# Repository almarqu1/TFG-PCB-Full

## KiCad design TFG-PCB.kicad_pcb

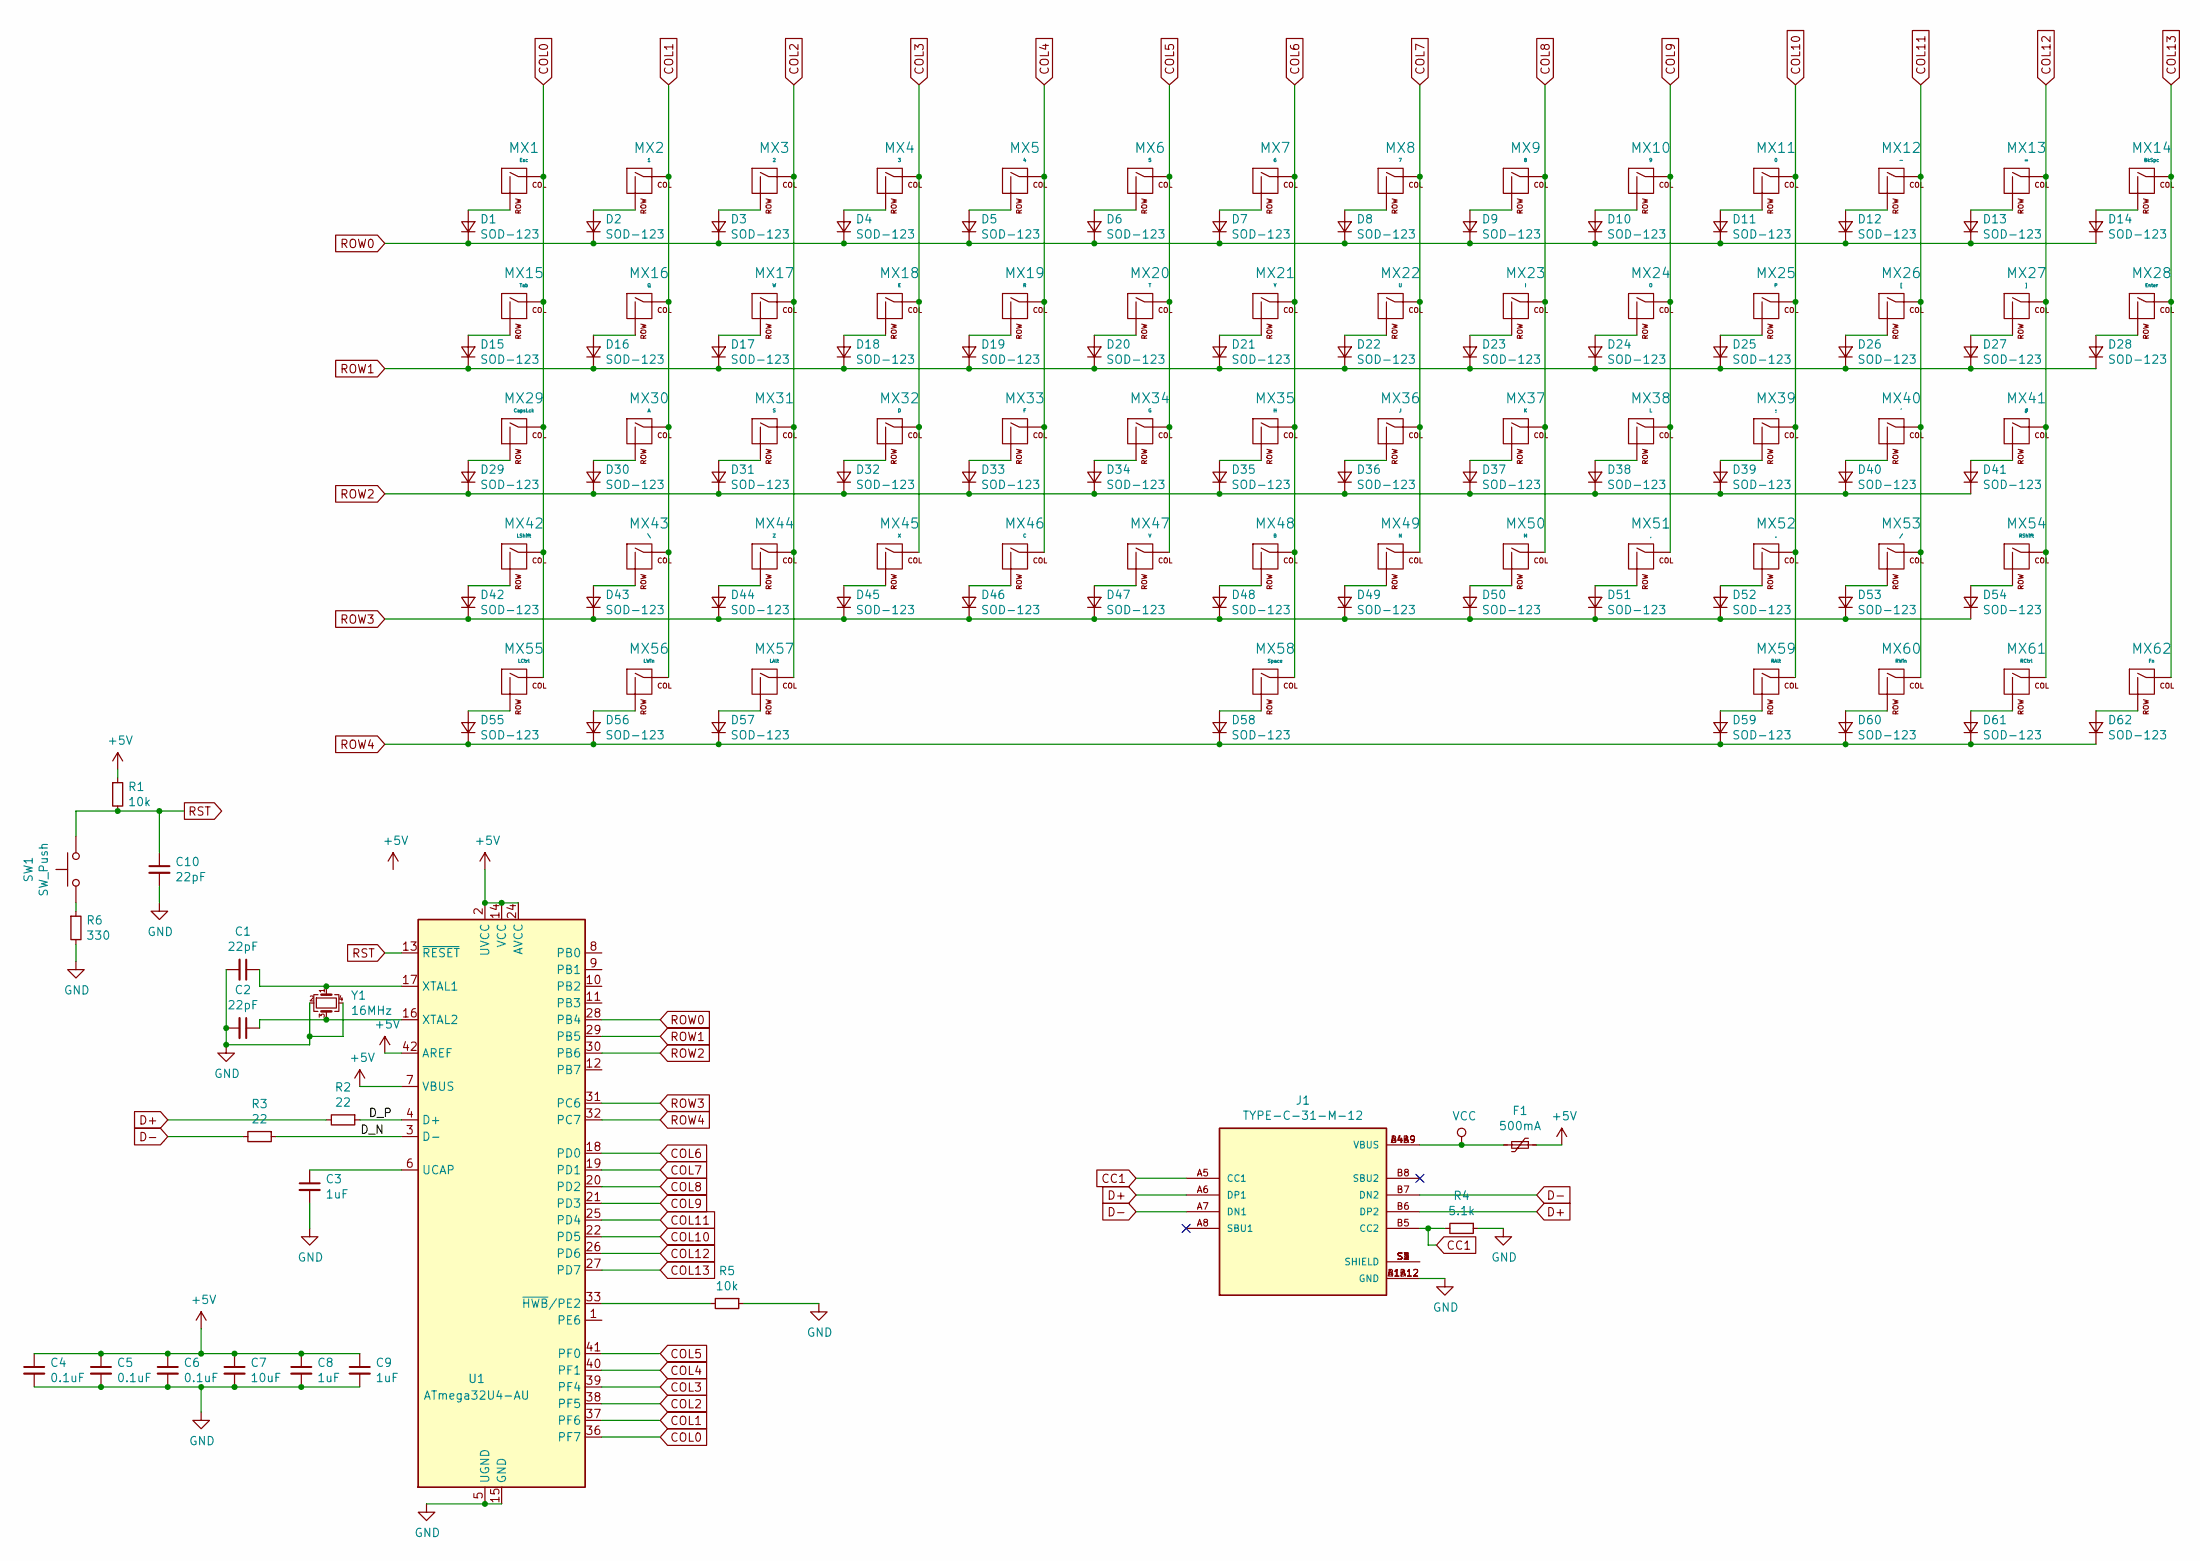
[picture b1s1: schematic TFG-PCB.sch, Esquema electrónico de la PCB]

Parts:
C1, C2, C10: 22pF; C_0805_2012Metric
C3, C8, C9: 1uF; C_0805_2012Metric
C4, C5, C6: 0.1uF; C_0805_2012Metric
C7: 10uF; C_0805_2012Metric
D1, D2, D3, D4, D5, D6, D7, D8, D9, D10, D11, D12, D13, D14, D15, D16, D17, D18, D19, D20, D21, D22, D23, D24, D25, D26, D27, D28, D29, D30, D31, D32, D33, D34, D35, D36, D37, D38, D39, D40, D41, D42, D43, D44, D45, D46, D47, D48, D49, D50, D51, D52, D53, D54, D55, D56, D57, D58, D59, D60, D61, D62: SOD-123; D_SOD-123
F1: 500mA; Fuse_1206_3216Metric
J1: TYPE-C-31-M-12; HRO_TYPE-C-31-M-12; PARTREV A
MX1: Esc; MXOnly-1U
MX2: 1; MXOnly-1U
MX3: 2; MXOnly-1U
MX4: 3; MXOnly-1U
MX5: 4; MXOnly-1U
MX6: 5; MXOnly-1U
MX7: 6; MXOnly-1U
MX8: 7; MXOnly-1U
MX9: 8; MXOnly-1U
MX10: 9; MXOnly-1U
MX11: 0; MXOnly-1U
MX12: -; MXOnly-1U
MX13: =; MXOnly-1U
MX14: BkSpc; MXOnly-2U
MX15: Tab; MXOnly-1.5U
MX16: Q; MXOnly-1U
MX17: W; MXOnly-1U
MX18: E; MXOnly-1U
MX19: R; MXOnly-1U
MX20: T; MXOnly-1U
MX21: Y; MXOnly-1U
MX22: U; MXOnly-1U
MX23: I; MXOnly-1U
MX24: O; MXOnly-1U
MX25: P; MXOnly-1U
MX26: [; MXOnly-1U
MX27: ]; MXOnly-1U
MX28: Enter; MXOnly-ISO
MX29: CapsLck; MXOnly-1.75U
MX30: A; MXOnly-1U
MX31: S; MXOnly-1U
MX32: D; MXOnly-1U
MX33: F; MXOnly-1U
MX34: G; MXOnly-1U
MX35: H; MXOnly-1U
MX36: J; MXOnly-1U
MX37: K; MXOnly-1U
MX38: L; MXOnly-1U
MX39: ;; MXOnly-1U
MX40: '; MXOnly-1U
MX41: #; MXOnly-1U
MX42: LShift; MXOnly-1.25U
MX43: \\; MXOnly-1U
MX44: Z; MXOnly-1U
MX45: X; MXOnly-1U
MX46: C; MXOnly-1U
MX47: V; MXOnly-1U
MX48: B; MXOnly-1U
MX49: N; MXOnly-1U
MX50: M; MXOnly-1U
MX51: ,; MXOnly-1U
MX52: .; MXOnly-1U
MX53: /; MXOnly-1U
MX54: RShift; MXOnly-2.75U
MX55: LCtrl; MXOnly-1.25U
MX56: LWin; MXOnly-1.25U
MX57: LAlt; MXOnly-1.25U
MX58: Space; MXOnly-6.25U
MX59: RAlt; MXOnly-1.25U
MX60: RWin; MXOnly-1.25U
MX61: RCtrl; MXOnly-1.25U
MX62: Fn; MXOnly-1.25U
R1, R5: 10k; R_0805_2012Metric
R2, R3: 22; R_0805_2012Metric
R4: 5.1k; R_0805_2012Metric
R6: 330; R_0805_2012Metric
SW1: SW_Push; SKQG-1155865
U1: ATmega32U4-AU; TQFP-44_10x10mm_P0.8mm
Y1: 16MHz; Crystal_SMD_3225-4Pin_3.2x2.5mm

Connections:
+5V: C4.1, C5.1, C6.1, C7.1, C8.1, C9.1, F1.1, R1.1, U1.2 (UVCC), U1.7 (VBUS), U1.14 (VCC), U1.24 (AVCC), U1.34 (VCC), U1.42 (AREF), U1.44 (AVCC)
/D_N: R3.1, U1.3 (D-)
/D_P: R2.1, U1.4 (D+)
CC1: J1.A5 (CC1), J1.B5 (CC2), R4.2
COL0: MX1.1 (COL), MX15.1 (COL), MX29.1 (COL), MX42.1 (COL), MX55.1 (COL), U1.36 (PF7)
COL1: MX2.1 (COL), MX16.1 (COL), MX30.1 (COL), MX43.1 (COL), MX56.1 (COL), U1.37 (PF6)
COL2: MX3.1 (COL), MX17.1 (COL), MX31.1 (COL), MX44.1 (COL), MX57.1 (COL), U1.38 (PF5)
COL3: MX4.1 (COL), MX18.1 (COL), MX32.1 (COL), MX45.1 (COL), U1.39 (PF4)
COL4: MX5.1 (COL), MX19.1 (COL), MX33.1 (COL), MX46.1 (COL), U1.40 (PF1)
COL5: MX6.1 (COL), MX20.1 (COL), MX34.1 (COL), MX47.1 (COL), U1.41 (PF0)
COL6: MX7.1 (COL), MX21.1 (COL), MX35.1 (COL), MX48.1 (COL), MX58.1 (COL), U1.18 (PD0)
COL7: MX8.1 (COL), MX22.1 (COL), MX36.1 (COL), MX49.1 (COL), U1.19 (PD1)
COL8: MX9.1 (COL), MX23.1 (COL), MX37.1 (COL), MX50.1 (COL), U1.20 (PD2)
COL9: MX10.1 (COL), MX24.1 (COL), MX38.1 (COL), MX51.1 (COL), U1.21 (PD3)
COL10: MX11.1 (COL), MX25.1 (COL), MX39.1 (COL), MX52.1 (COL), MX59.1 (COL), U1.22 (PD5)
COL11: MX12.1 (COL), MX26.1 (COL), MX40.1 (COL), MX53.1 (COL), MX60.1 (COL), U1.25 (PD4)
COL12: MX13.1 (COL), MX27.1 (COL), MX41.1 (COL), MX54.1 (COL), MX61.1 (COL), U1.26 (PD6)
COL13: MX14.1 (COL), MX28.1 (COL), MX62.1 (COL), U1.27 (PD7)
D+: J1.A6 (DP1), J1.B6 (DP2), R2.2
D-: J1.A7 (DN1), J1.B7 (DN2), R3.2
GND: C1.2, C2.2, C3.2, C4.2, C5.2, C6.2, C7.2, C8.2, C9.2, C10.2, J1.A1B12 (GND), J1.B1A12 (GND), R4.1, R5.1, R6.2, U1.5 (UGND), U1.15 (GND), U1.23 (GND), U1.35 (GND), U1.43 (GND), Y1.2, Y1.4
unnamed: C1.1, U1.17 (XTAL1), Y1.1
unnamed: C2.1, U1.16 (XTAL2), Y1.3
unnamed: C3.1, U1.6 (UCAP)
unnamed: D1.2 (A), MX1.2 (ROW)
unnamed: D2.2 (A), MX2.2 (ROW)
unnamed: D3.2 (A), MX3.2 (ROW)
unnamed: D4.2 (A), MX4.2 (ROW)
unnamed: D5.2 (A), MX5.2 (ROW)
unnamed: D6.2 (A), MX6.2 (ROW)
unnamed: D7.2 (A), MX7.2 (ROW)
unnamed: D8.2 (A), MX8.2 (ROW)
unnamed: D9.2 (A), MX9.2 (ROW)
unnamed: D10.2 (A), MX10.2 (ROW)
unnamed: D11.2 (A), MX11.2 (ROW)
unnamed: D12.2 (A), MX12.2 (ROW)
unnamed: D13.2 (A), MX13.2 (ROW)
unnamed: D14.2 (A), MX14.2 (ROW)
unnamed: D15.2 (A), MX15.2 (ROW)
unnamed: D16.2 (A), MX16.2 (ROW)
unnamed: D17.2 (A), MX17.2 (ROW)
unnamed: D18.2 (A), MX18.2 (ROW)
unnamed: D19.2 (A), MX19.2 (ROW)
unnamed: D20.2 (A), MX20.2 (ROW)
unnamed: D21.2 (A), MX21.2 (ROW)
unnamed: D22.2 (A), MX22.2 (ROW)
unnamed: D23.2 (A), MX23.2 (ROW)
unnamed: D24.2 (A), MX24.2 (ROW)
unnamed: D25.2 (A), MX25.2 (ROW)
unnamed: D26.2 (A), MX26.2 (ROW)
unnamed: D27.2 (A), MX27.2 (ROW)
unnamed: D28.2 (A), MX28.2 (ROW)
unnamed: D29.2 (A), MX29.2 (ROW)
unnamed: D30.2 (A), MX30.2 (ROW)
unnamed: D31.2 (A), MX31.2 (ROW)
unnamed: D32.2 (A), MX32.2 (ROW)
unnamed: D33.2 (A), MX33.2 (ROW)
unnamed: D34.2 (A), MX34.2 (ROW)
unnamed: D35.2 (A), MX35.2 (ROW)
unnamed: D36.2 (A), MX36.2 (ROW)
unnamed: D37.2 (A), MX37.2 (ROW)
unnamed: D38.2 (A), MX38.2 (ROW)
unnamed: D39.2 (A), MX39.2 (ROW)
unnamed: D40.2 (A), MX40.2 (ROW)
unnamed: D41.2 (A), MX41.2 (ROW)
unnamed: D42.2 (A), MX42.2 (ROW)
unnamed: D43.2 (A), MX43.2 (ROW)
unnamed: D44.2 (A), MX44.2 (ROW)
unnamed: D45.2 (A), MX45.2 (ROW)
unnamed: D46.2 (A), MX46.2 (ROW)
unnamed: D47.2 (A), MX47.2 (ROW)
unnamed: D48.2 (A), MX48.2 (ROW)
unnamed: D49.2 (A), MX49.2 (ROW)
unnamed: D50.2 (A), MX50.2 (ROW)
unnamed: D51.2 (A), MX51.2 (ROW)
unnamed: D52.2 (A), MX52.2 (ROW)
unnamed: D53.2 (A), MX53.2 (ROW)
unnamed: D54.2 (A), MX54.2 (ROW)
unnamed: D55.2 (A), MX55.2 (ROW)
unnamed: D56.2 (A), MX56.2 (ROW)
unnamed: D57.2 (A), MX57.2 (ROW)
unnamed: D58.2 (A), MX58.2 (ROW)
unnamed: D59.2 (A), MX59.2 (ROW)
unnamed: D60.2 (A), MX60.2 (ROW)
unnamed: D61.2 (A), MX61.2 (ROW)
unnamed: D62.2 (A), MX62.2 (ROW)
unnamed: J1.S1 (SHIELD), J1.S2 (SHIELD), J1.S3 (SHIELD), J1.S4 (SHIELD)
unnamed: R5.2, U1.33 (~HWB~/PE2)
unnamed: R6.1, SW1.1
ROW0: D1.1 (K), D2.1 (K), D3.1 (K), D4.1 (K), D5.1 (K), D6.1 (K), D7.1 (K), D8.1 (K), D9.1 (K), D10.1 (K), D11.1 (K), D12.1 (K), D13.1 (K), D14.1 (K), U1.28 (PB4)
ROW1: D15.1 (K), D16.1 (K), D17.1 (K), D18.1 (K), D19.1 (K), D20.1 (K), D21.1 (K), D22.1 (K), D23.1 (K), D24.1 (K), D25.1 (K), D26.1 (K), D27.1 (K), D28.1 (K), U1.29 (PB5)
ROW2: D29.1 (K), D30.1 (K), D31.1 (K), D32.1 (K), D33.1 (K), D34.1 (K), D35.1 (K), D36.1 (K), D37.1 (K), D38.1 (K), D39.1 (K), D40.1 (K), D41.1 (K), U1.30 (PB6)
ROW3: D42.1 (K), D43.1 (K), D44.1 (K), D45.1 (K), D46.1 (K), D47.1 (K), D48.1 (K), D49.1 (K), D50.1 (K), D51.1 (K), D52.1 (K), D53.1 (K), D54.1 (K), U1.31 (PC6)
ROW4: D55.1 (K), D56.1 (K), D57.1 (K), D58.1 (K), D59.1 (K), D60.1 (K), D61.1 (K), D62.1 (K), U1.32 (PC7)
RST: C10.1, R1.2, SW1.2, U1.13 (~RESET)
VCC: F1.2, J1.A4B9 (VBUS), J1.B4A9 (VBUS)

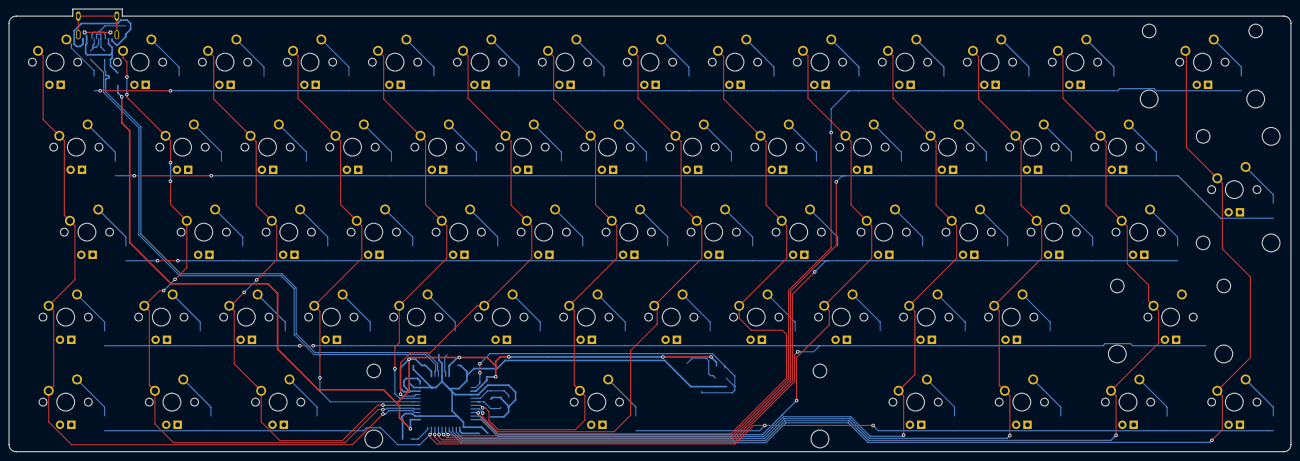
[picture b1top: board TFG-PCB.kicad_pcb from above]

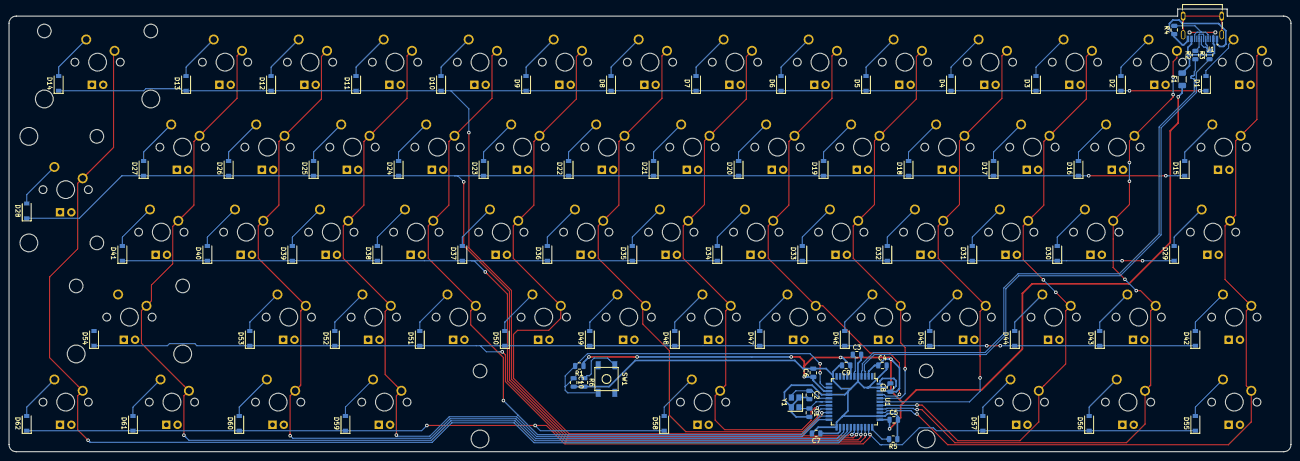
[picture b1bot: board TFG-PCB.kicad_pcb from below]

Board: 2 copper layers, 287.3 x 99.2 mm, 145 parts (83 on the bottom side), 96 nets.

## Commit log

2021-08-13 Added 60% keyboard schematics and started routing wires
2021-08-25 Renamed Footprints to account for keys
2021-08-25 Edge cuts + wiring removal
    Removed all wires, slightly adjusted diode positions so they fit outside the switch courtyards + created the edge cuts that represent the board edges
2021-08-27 Moved diodes + started wiring
    Moved diodes (again) and started differential wiring
2021-08-27 Wired USB
    Finished differential wiring + skew
2021-08-27 Rewiring + moving diodes
    Moved diodes (for the last time i think) and started wiring MC
2021-08-28 Almost all wiring done
    Practically finished wiring
2021-08-28 Remade Reset button circuit
2021-08-29 PCB finished (almost)
    PCB finished aside from ground fill and logo addition
2021-08-30 Board created!
    Included logo, fixed minor issues, generated board files + zipped gerbers into folder
